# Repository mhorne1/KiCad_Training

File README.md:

# KiCad_Training
Schematic Capture and PCB Layout

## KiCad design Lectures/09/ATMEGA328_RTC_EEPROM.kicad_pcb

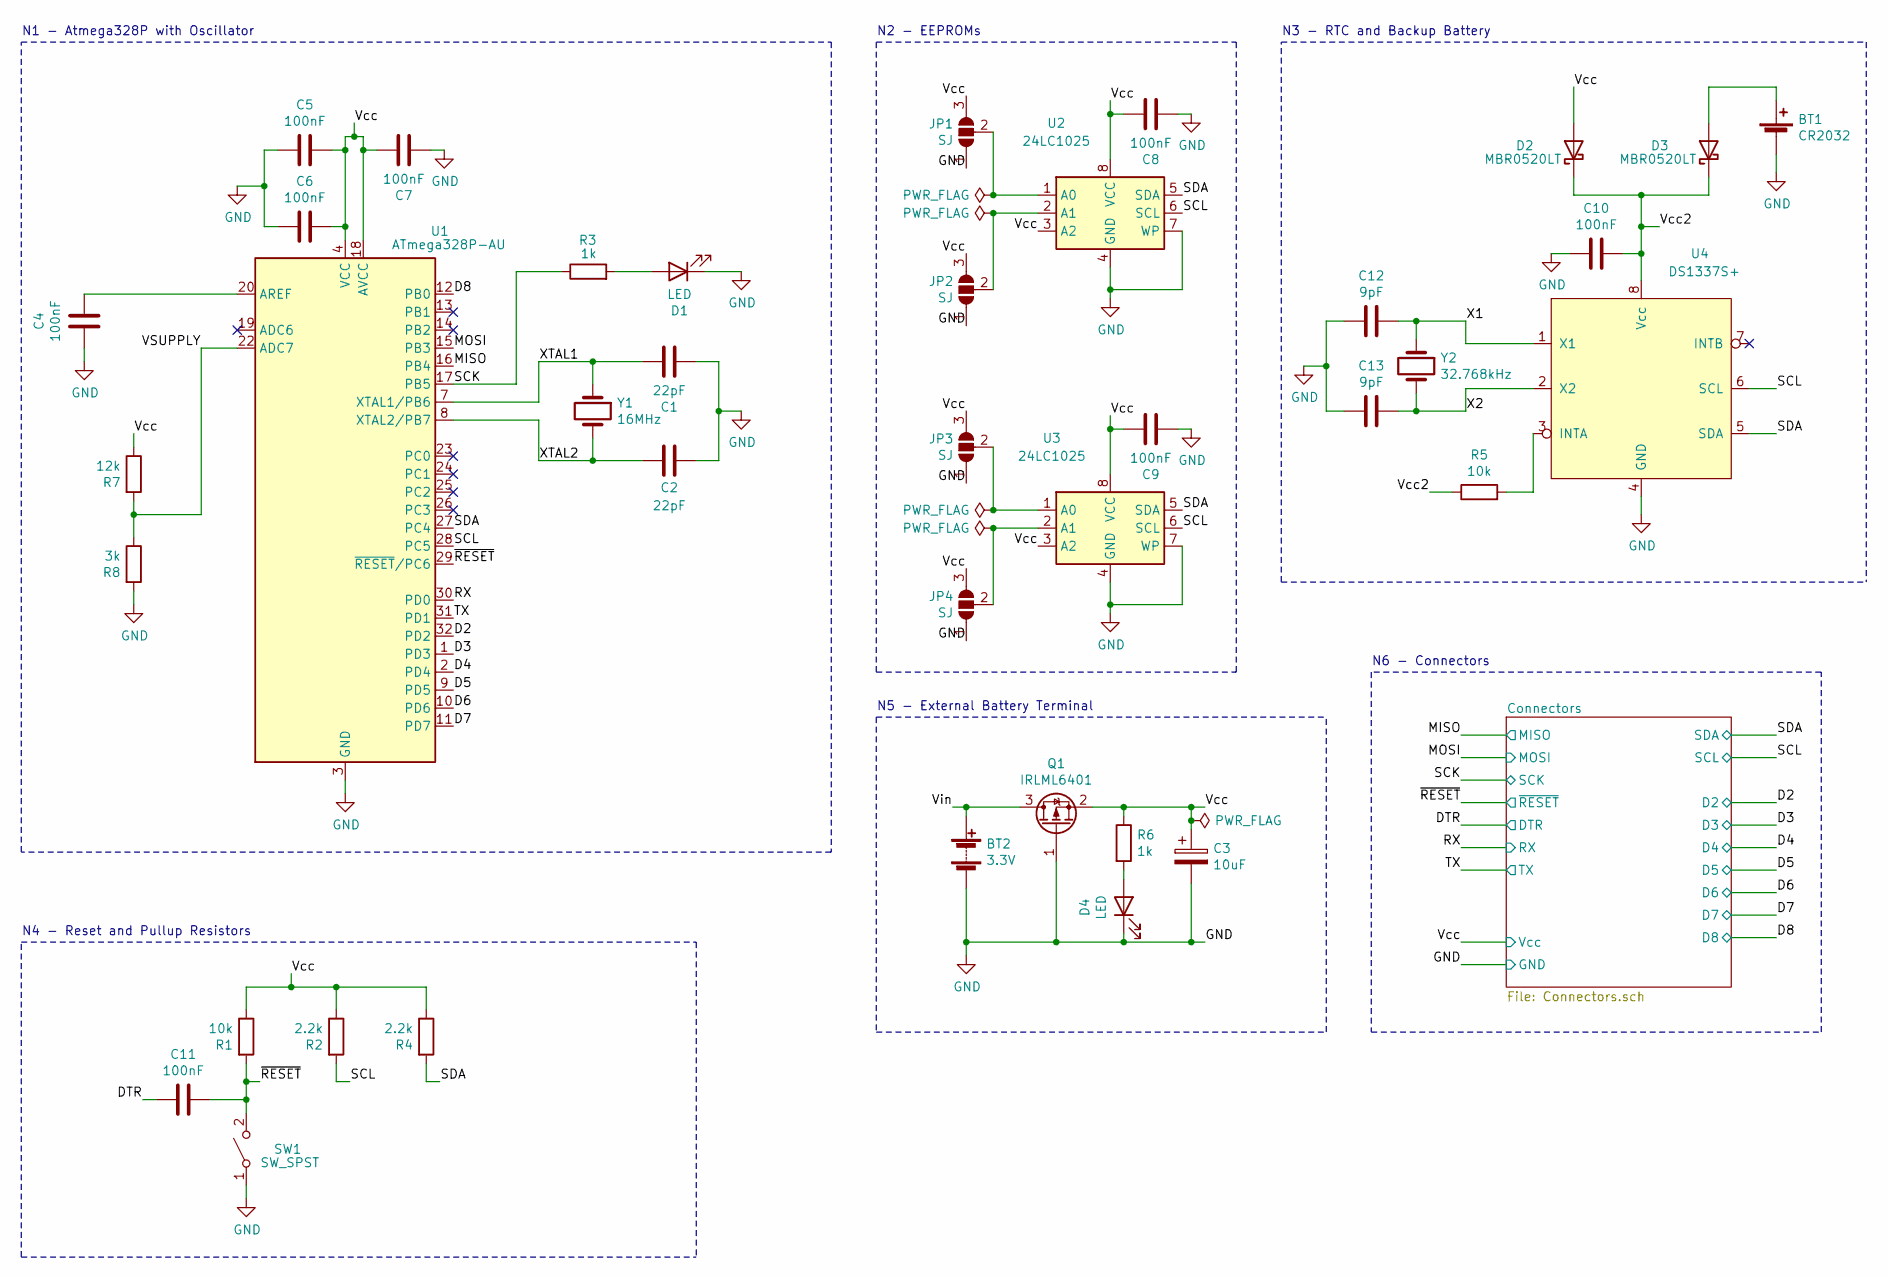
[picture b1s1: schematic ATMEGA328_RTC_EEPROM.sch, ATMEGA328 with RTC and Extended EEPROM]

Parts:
BT1: CR2032; BatteryHolder_Keystone_1058_1x2032
BT2: 3.3V; PinSocket_1x02_P2.54mm_Vertical
C1, C2: 22pF; C_0603_1608Metric
C3: 10uF; C_0805_2012Metric
C4, C5, C6, C7, C8, C9, C10, C11: 100nF; C_0603_1608Metric
C12, C13: 9pF; C_0603_1608Metric
D1, D4: LED; LED_0805_2012Metric
D2, D3: MBR0520LT; D_SOD-123
JP1, JP2, JP3, JP4: SJ; SolderJumper-3_P1.3mm_Open_Pad1.0x1.5mm
Q1: IRLML6401; SOT-23
R1, R5: 10k; R_0805_2012Metric
R2, R4: 2.2k; R_0805_2012Metric
R3, R6: 1k; R_0805_2012Metric
R7: 12k; R_0805_2012Metric
R8: 3k; R_0805_2012Metric
SW1: SW_SPST; SW_SPST_PTS645
U1: ATmega328P-AU; TQFP-32_7x7mm_P0.8mm
U2, U3: 24LC1025; SOIJ-8_5.3x5.3mm_P1.27mm
U4: DS1337S+; SO-8_5.3x6.2mm_P1.27mm
Y1: 16MHz; Crystal_SMD_5032-2Pin_5.0x3.2mm
Y2: 32.768kHz; Crystal_SMD_MicroCrystal_CC7V-T1A-2Pin_3.2x1.5mm

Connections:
/D2: U1.32 (PD2); also elsewhere on the board
/D3: U1.1 (PD3); also elsewhere on the board
/D4: U1.2 (PD4); also elsewhere on the board
/D5: U1.9 (PD5); also elsewhere on the board
/D6: U1.10 (PD6); also elsewhere on the board
/D7: U1.11 (PD7); also elsewhere on the board
/D8: U1.12 (PB0); also elsewhere on the board
/DTR: C11.2; also elsewhere on the board
/MISO: U1.16 (PB4); also elsewhere on the board
/MOSI: U1.15 (PB3); also elsewhere on the board
/RX: U1.30 (PD0); also elsewhere on the board
/SCK: R3.1, U1.17 (PB5); also elsewhere on the board
/SCL: R2.2, U1.28 (PC5), U2.6 (SCL), U3.6 (SCL), U4.6 (SCL); also elsewhere on the board
/SDA: R4.2, U1.27 (PC4), U2.5 (SDA), U3.5 (SDA), U4.5 (SDA); also elsewhere on the board
/TX: U1.31 (PD1); also elsewhere on the board
/VSUPPLY: R7.2, R8.1, U1.22 (ADC7)
/Vcc: C3.1, C5.1, C6.1, C7.1, C8.1, C9.1, D2.2 (A), JP1.3 (B), JP2.3 (B), JP3.3 (B), JP4.3 (B), Q1.2 (S), R1.1, R2.1, R4.1, R6.1, R7.1, U1.4 (VCC), U1.6 (VCC), U1.18 (AVCC), U2.3 (A2), U2.8 (VCC), U3.3 (A2), U3.8 (VCC); also elsewhere on the board
/Vcc2: C10.1, D2.1 (K), D3.1 (K), R5.1, U4.8 (Vcc)
/Vin: BT2.1 (+), Q1.3 (D)
/X1: C12.1, U4.1 (X1), Y2.1
/X2: C13.1, U4.2 (X2), Y2.2
/XTAL1: C1.1, U1.7 (XTAL1/PB6), Y1.1
/XTAL2: C2.1, U1.8 (XTAL2/PB7), Y1.2
/~RESET: C11.1, R1.2, SW1.2 (B), U1.29 (~RESET~/PC6); also elsewhere on the board
GND: BT1.2 (-), BT2.2 (-), C1.2, C2.2, C3.2, C4.2, C5.2, C6.2, C7.2, C8.2, C9.2, C10.2, C12.2, C13.2, D1.1 (K), D4.1 (K), JP1.1 (A), JP2.1 (A), JP3.1 (A), JP4.1 (A), Q1.1 (G), R8.2, SW1.1 (A), U1.3 (GND), U1.5 (GND), U1.21 (GND), U2.4 (GND), U2.7 (WP), U3.4 (GND), U3.7 (WP), U4.4 (GND); also elsewhere on the board
unnamed: BT1.1 (+), D3.2 (A)
unnamed: C4.1, U1.20 (AREF)
unnamed: D1.2 (A), R3.2
unnamed: D4.2 (A), R6.2
unnamed: JP1.2 (C), U2.1 (A0)
unnamed: JP2.2 (C), U2.2 (A1)
unnamed: JP3.2 (C), U3.1 (A0)
unnamed: JP4.2 (C), U3.2 (A1)
unnamed: R5.2, U4.3 (INTA)

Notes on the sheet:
N5 - External Battery Terminal
N6 - Connectors
N4 - Reset and Pullup Resistors
N3 - RTC and Backup Battery
N2 - EEPROMs
N1 - Atmega328P with Oscillator

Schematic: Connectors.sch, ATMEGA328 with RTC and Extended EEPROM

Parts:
H1, H2, H3, H4: MountingHole_Pad; MountingHole_2.2mm_M2_Pad_Via
J1: Serial; PinHeader_1x06_P2.54mm_Vertical
J2: Digital Pins; PinSocket_1x09_P2.54mm_Vertical
J3: I2C; PinSocket_1x04_P2.54mm_Vertical
J4: ICSP; PinHeader_2x03_P2.54mm_Vertical

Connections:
/D2: J2.1; also elsewhere on the board
/D3: J2.3; also elsewhere on the board
/D4: J2.5; also elsewhere on the board
/DTR: J1.6; also elsewhere on the board
/MISO: J4.1; also elsewhere on the board
/MOSI: J4.4; also elsewhere on the board
/RX: J1.4; also elsewhere on the board
/SCK: J4.3; also elsewhere on the board
/SCL: J3.4; also elsewhere on the board
/SDA: J3.3; also elsewhere on the board
/TX: J1.5; also elsewhere on the board
/Vcc: J1.3, J3.2, J4.2; also elsewhere on the board
/~RESET: J4.5; also elsewhere on the board
GND: H1.1, H2.1, H3.1, H4.1, J1.1, J1.2, J2.2, J2.4, J2.6, J3.1, J4.6; also elsewhere on the board

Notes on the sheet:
N7 - Serial Connector
N8 - I2C Connector
N9 - GPIO Connector
N10 - SPI Connector
N11 - Mounting Holes

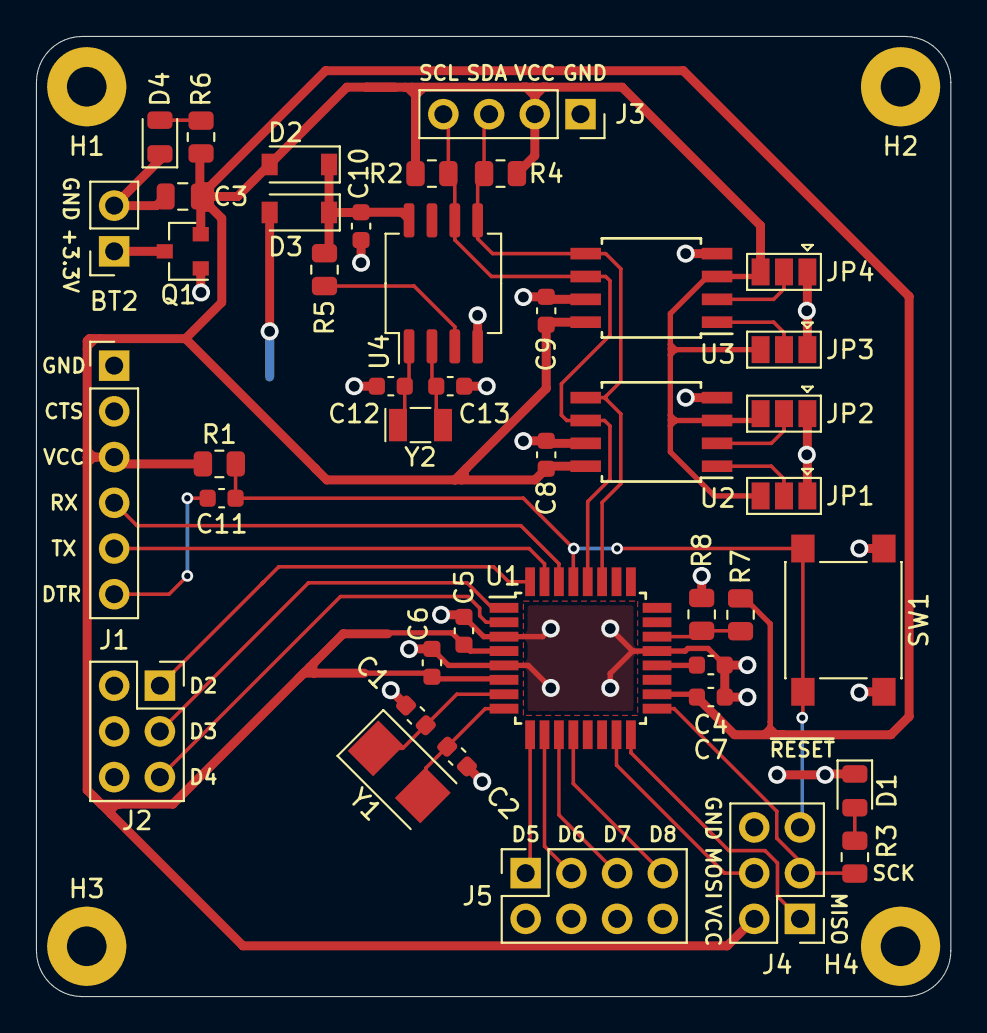
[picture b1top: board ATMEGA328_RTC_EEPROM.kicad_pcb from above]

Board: 2 copper layers, 50.8 x 53.3 mm, 48 parts (1 on the bottom side), 34 nets.

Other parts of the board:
J5: Digital 2; PinSocket_2x04_P2.54mm_Vertical

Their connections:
/D5: J5.1; also elsewhere on the board
/D6: J5.3; also elsewhere on the board
/D7: J5.5; also elsewhere on the board
/D8: J5.7; also elsewhere on the board
GND: J5.2, J5.4, J5.6, J5.8; also elsewhere on the board

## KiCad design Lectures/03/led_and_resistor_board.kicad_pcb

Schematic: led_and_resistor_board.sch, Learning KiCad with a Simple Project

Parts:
D1: LED; LED_D8.0mm
J1: Conn_01x02_Male; TerminalBlock_bornier-2_P5.08mm
R1: R; R_Axial_DIN0204_L3.6mm_D1.6mm_P5.08mm_Horizontal

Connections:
+5V: J1.2, R1.1
GND: D1.1 (K), J1.1
unnamed: D1.2 (A), R1.2

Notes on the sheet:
A Simple LED Resistor Schematic

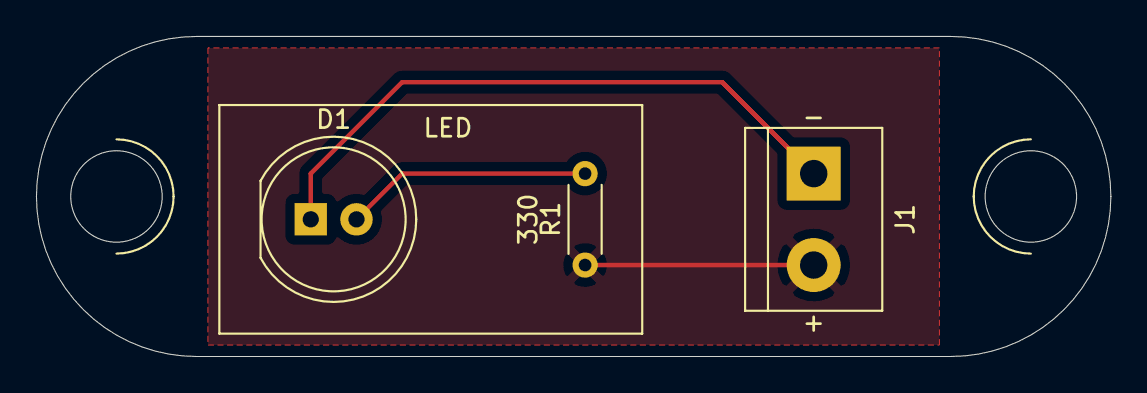
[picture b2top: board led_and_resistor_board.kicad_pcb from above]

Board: 2 copper layers, 59.7 x 17.8 mm, 3 parts (0 on the bottom side), 3 nets.

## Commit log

2021-01-06 Layout
2021-01-07 Terminal Block
2021-01-19 Raspberry Pi HAT Schematic
2021-01-20 Gerber files for Raspberry Pi HAT
2021-01-20 Raspberry PI HAT layout files and updates
2021-01-21 Symbol for DS1337S+
2021-01-21 Schematic for ATMEGA328 with RTC and EEPROMs
2021-01-21 Included decoupling capacitors
2021-01-23 Reverse Input Voltage Polarity Protection
2021-01-24 2-Layer AR Layout
2021-01-25 4-Layer AR Layout
2021-01-27 Schematic updates
2021-01-29 RTC loading capacitors
2021-02-03 ATMEGA328 Layout
2021-02-03 Addressing and Silkscreen
2021-02-03 Gerber Files
2021-03-04 EEPROM addresses set by jumpers
